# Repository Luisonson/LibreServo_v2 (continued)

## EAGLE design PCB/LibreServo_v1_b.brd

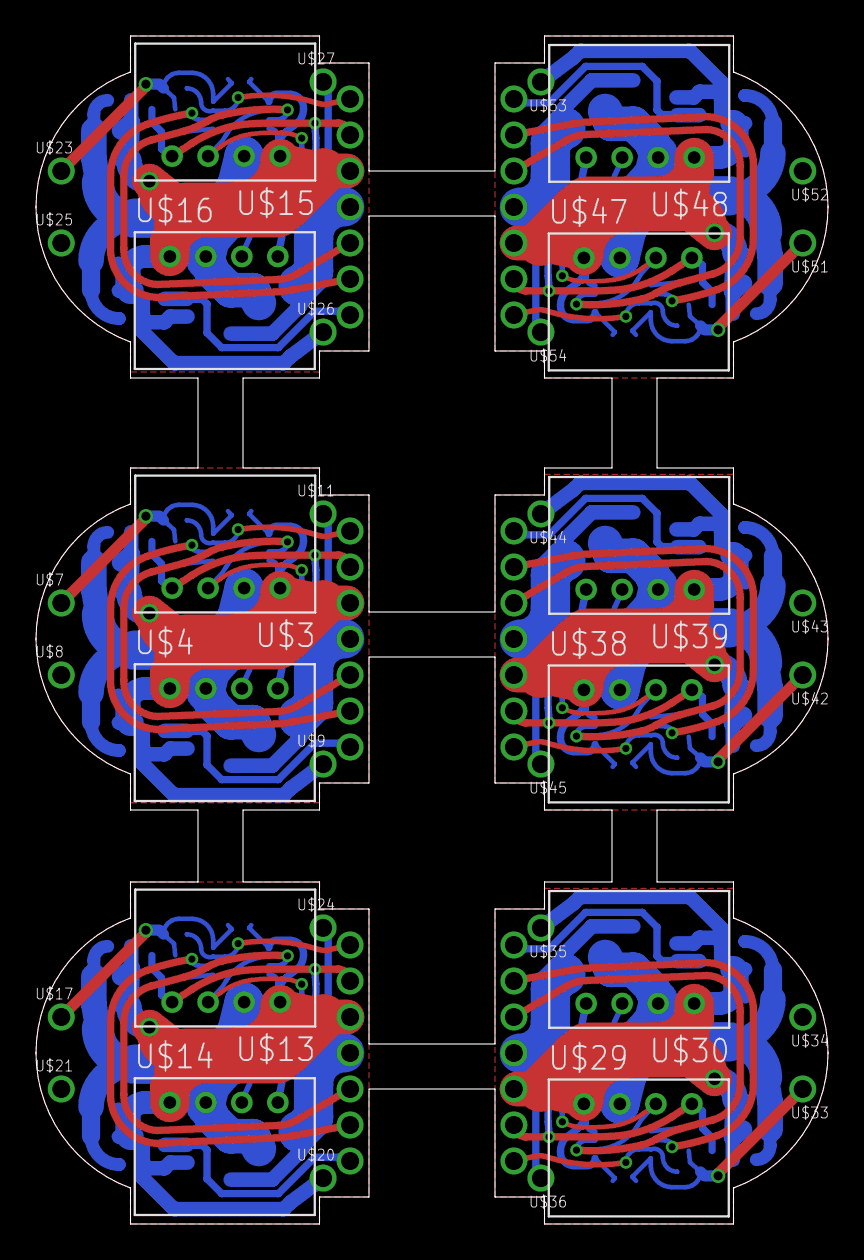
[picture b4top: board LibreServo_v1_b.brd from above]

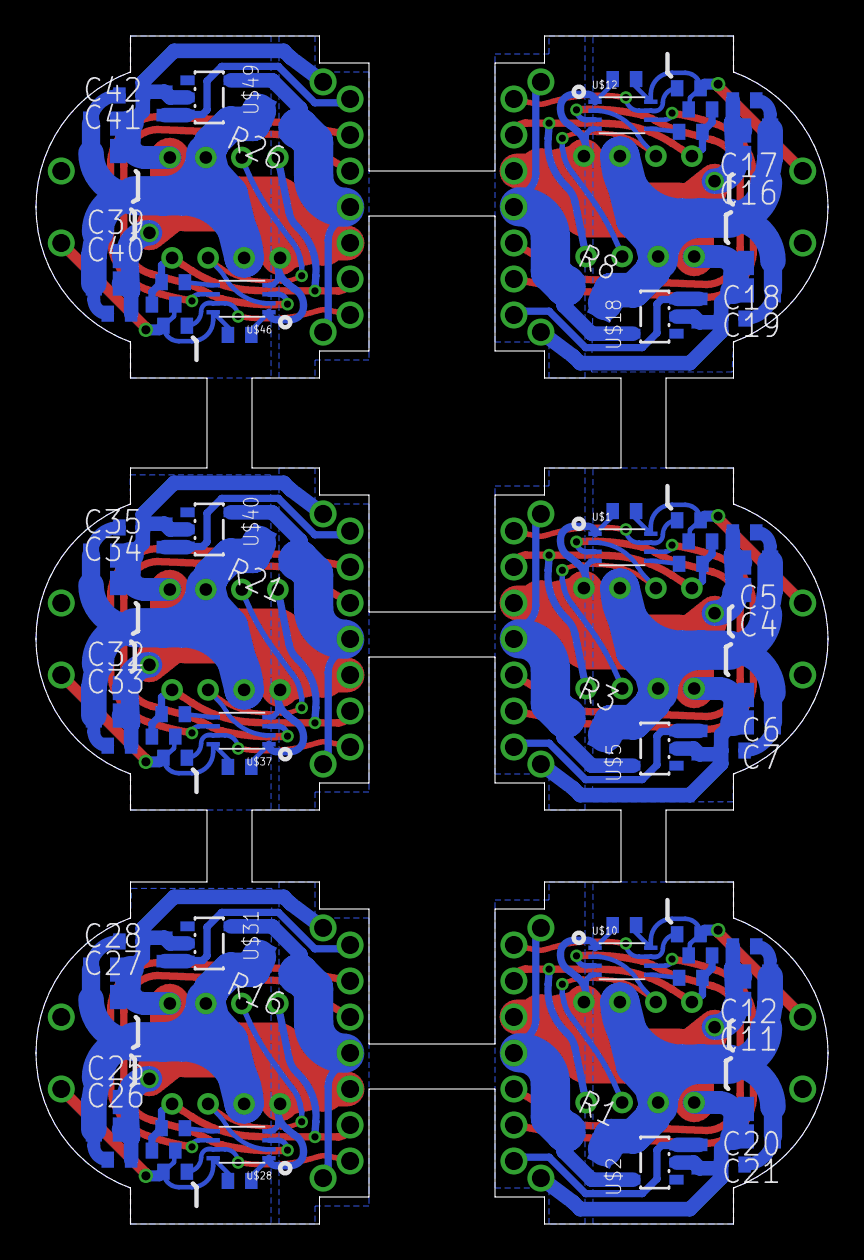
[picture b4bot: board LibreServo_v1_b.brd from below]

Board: 2 copper layers, 44.0 x 66.0 mm, 126 parts (84 on the bottom side), 66 nets.

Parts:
C1, C2, C3, C8, C9, C10, C13, C14, C15, C22, C23, C24, C29, C30, C31, C36, C37, C38: 100nF; C0402
C4, C5, C6, C7, C11, C12, C16, C17, C18, C19, C20, C21, C25, C26, C27, C28, C32, C33, C34, C35, C39, C40, C41, C42: 22uF; 0805_MIN
R1, R3, R8, R16, R21, R26: 0.02; 1206_ESTRECHA
R2, R4, R9, R17, R22, R27: 1k1; R0402
R5, R10, R11, R18, R23, R28: 10K; R0402
R6, R12, R14, R19, R24, R29: 100; R0402
R7, R13, R15, R20, R25, R30: 100K; R0402
U$1, U$10, U$12, U$28, U$37, U$46: SN74LVC2G125; VSSOP-8
U$2, U$5, U$18, U$31, U$40, U$49: ZXCT1010; SOT25
U$3, U$4, U$13, U$14, U$15, U$16, U$29, U$30, U$38, U$39, U$47, U$48: JST_PH-4; JST_PH-4_HOLE
U$6, U$19, U$22, U$32, U$41, U$50: HEADER_7_MIN
U$7, U$8, U$9, U$11, U$17, U$20, U$21, U$23, U$24, U$25, U$26, U$27, U$33, U$34, U$35, U$36, U$42, U$43, U$44, U$45, U$51, U$52, U$53, U$54: HEADER_1_MIN

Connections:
+3V3_1: C3.1, R5.1, R7.2, U$1.P$8, U$7.P$1
+3V3_2: C15.1, R11.1, R13.2, U$10.P$8, U$17.P$1
+3V3_3: C10.1, R10.1, R15.2, U$12.P$8, U$23.P$1
+3V3_4: C24.1, R18.1, R20.2, U$28.P$8, U$33.P$1
+3V3_5: C31.1, R23.1, R25.2, U$37.P$8, U$42.P$1
+3V3_6: C38.1, R28.1, R30.2, U$46.P$8, U$51.P$1
+7V_1: R3.1, U$5.5, U$6.P$4, U$11.P$1
+7V_2: R1.1, U$2.5, U$19.P$4, U$24.P$1
+7V_2_CABLE: C11.1, C12.1, C13.1, C14.1, C20.1, C21.1, R1.2, U$2.4, U$13.P$2, U$14.P$2
+7V_2_CABLE1: C1.1, C2.1, C4.1, C5.1, C6.1, C7.1, R3.2, U$3.P$2, U$4.P$2, U$5.4
+7V_2_CABLE2: C8.1, C9.1, C16.1, C17.1, C18.1, C19.1, R8.2, U$15.P$2, U$16.P$2, U$18.4
+7V_2_CABLE3: C22.1, C23.1, C25.1, C26.1, C27.1, C28.1, R16.2, U$29.P$2, U$30.P$2, U$31.4
+7V_2_CABLE4: C29.1, C30.1, C32.1, C33.1, C34.1, C35.1, R21.2, U$38.P$2, U$39.P$2, U$40.4
+7V_2_CABLE5: C36.1, C37.1, C39.1, C40.1, C41.1, C42.1, R26.2, U$47.P$2, U$48.P$2, U$49.4
+7V_3: R8.1, U$18.5, U$22.P$4, U$27.P$1
+7V_4: R16.1, U$31.5, U$32.P$4, U$36.P$1
+7V_5: R21.1, U$40.5, U$41.P$4, U$45.P$1
+7V_6: R26.1, U$49.5, U$50.P$4, U$54.P$1
EN_SERIAL_1: R5.2, U$1.P$7, U$6.P$1
EN_SERIAL_2: R11.2, U$10.P$7, U$19.P$1
EN_SERIAL_3: R10.2, U$12.P$7, U$22.P$1
EN_SERIAL_4: R18.2, U$28.P$7, U$32.P$1
EN_SERIAL_5: R23.2, U$37.P$7, U$41.P$1
EN_SERIAL_6: R28.2, U$46.P$7, U$50.P$1
GND1: C1.2, C2.2, C3.2, C4.2, C5.2, C6.2, C7.2, R4.1, U$1.P$1, U$1.P$4, U$3.P$1, U$4.P$1, U$5.2, U$6.P$3, U$9.P$1
GND2: C11.2, C12.2, C13.2, C14.2, C15.2, C20.2, C21.2, R2.1, U$2.2, U$10.P$1, U$10.P$4, U$13.P$1, U$14.P$1, U$19.P$3, U$20.P$1
GND3: C8.2, C9.2, C10.2, C16.2, C17.2, C18.2, C19.2, R9.1, U$12.P$1, U$12.P$4, U$15.P$1, U$16.P$1, U$18.2, U$22.P$3, U$26.P$1
GND4: C22.2, C23.2, C24.2, C25.2, C26.2, C27.2, C28.2, R17.1, U$28.P$1, U$28.P$4, U$29.P$1, U$30.P$1, U$31.2, U$32.P$3, U$35.P$1
GND5: C29.2, C30.2, C31.2, C32.2, C33.2, C34.2, C35.2, R22.1, U$37.P$1, U$37.P$4, U$38.P$1, U$39.P$1, U$40.2, U$41.P$3, U$44.P$1
GND6: C36.2, C37.2, C38.2, C39.2, C40.2, C41.2, C42.2, R27.1, U$46.P$1, U$46.P$4, U$47.P$1, U$48.P$1, U$49.2, U$50.P$3, U$53.P$1
unnamed: R6.1, U$1.P$5
unnamed: R14.1, U$12.P$5
unnamed: R19.1, U$28.P$5
unnamed: R24.1, U$37.P$5
unnamed: R29.1, U$46.P$5
unnamed: R12.1, U$10.P$5
RX_1: U$1.P$6, U$6.P$6
RX_2: U$10.P$6, U$19.P$6
RX_2_CABLE: U$10.P$2, U$13.P$3, U$14.P$3
RX_2_CABLE1: U$1.P$2, U$3.P$3, U$4.P$3
RX_2_CABLE2: U$12.P$2, U$15.P$3, U$16.P$3
RX_2_CABLE3: U$28.P$2, U$29.P$3, U$30.P$3
RX_2_CABLE4: U$37.P$2, U$38.P$3, U$39.P$3
RX_2_CABLE5: U$46.P$2, U$47.P$3, U$48.P$3
RX_3: U$12.P$6, U$22.P$6
RX_4: U$28.P$6, U$32.P$6
RX_5: U$37.P$6, U$41.P$6
RX_6: U$46.P$6, U$50.P$6
TX_1: U$1.P$3, U$6.P$5
TX_2: U$10.P$3, U$19.P$5
TX_2_CABLE: R12.2, R13.1, U$13.P$4, U$14.P$4, U$19.P$2
TX_2_CABLE1: R6.2, R7.1, U$3.P$4, U$4.P$4, U$6.P$2
TX_2_CABLE2: R14.2, R15.1, U$15.P$4, U$16.P$4, U$22.P$2
TX_2_CABLE3: R19.2, R20.1, U$29.P$4, U$30.P$4, U$32.P$2
TX_2_CABLE4: R24.2, R25.1, U$38.P$4, U$39.P$4, U$41.P$2
TX_2_CABLE5: R29.2, R30.1, U$47.P$4, U$48.P$4, U$50.P$2
TX_3: U$12.P$3, U$22.P$5
TX_4: U$28.P$3, U$32.P$5
TX_5: U$37.P$3, U$41.P$5
TX_6: U$46.P$3, U$50.P$5
V_CORRIENTE_1: R4.2, U$5.3, U$6.P$7
V_CORRIENTE_2: R2.2, U$2.3, U$19.P$7
V_CORRIENTE_3: R9.2, U$18.3, U$22.P$7
V_CORRIENTE_4: R17.2, U$31.3, U$32.P$7
V_CORRIENTE_5: R22.2, U$40.3, U$41.P$7
V_CORRIENTE_6: R27.2, U$49.3, U$50.P$7

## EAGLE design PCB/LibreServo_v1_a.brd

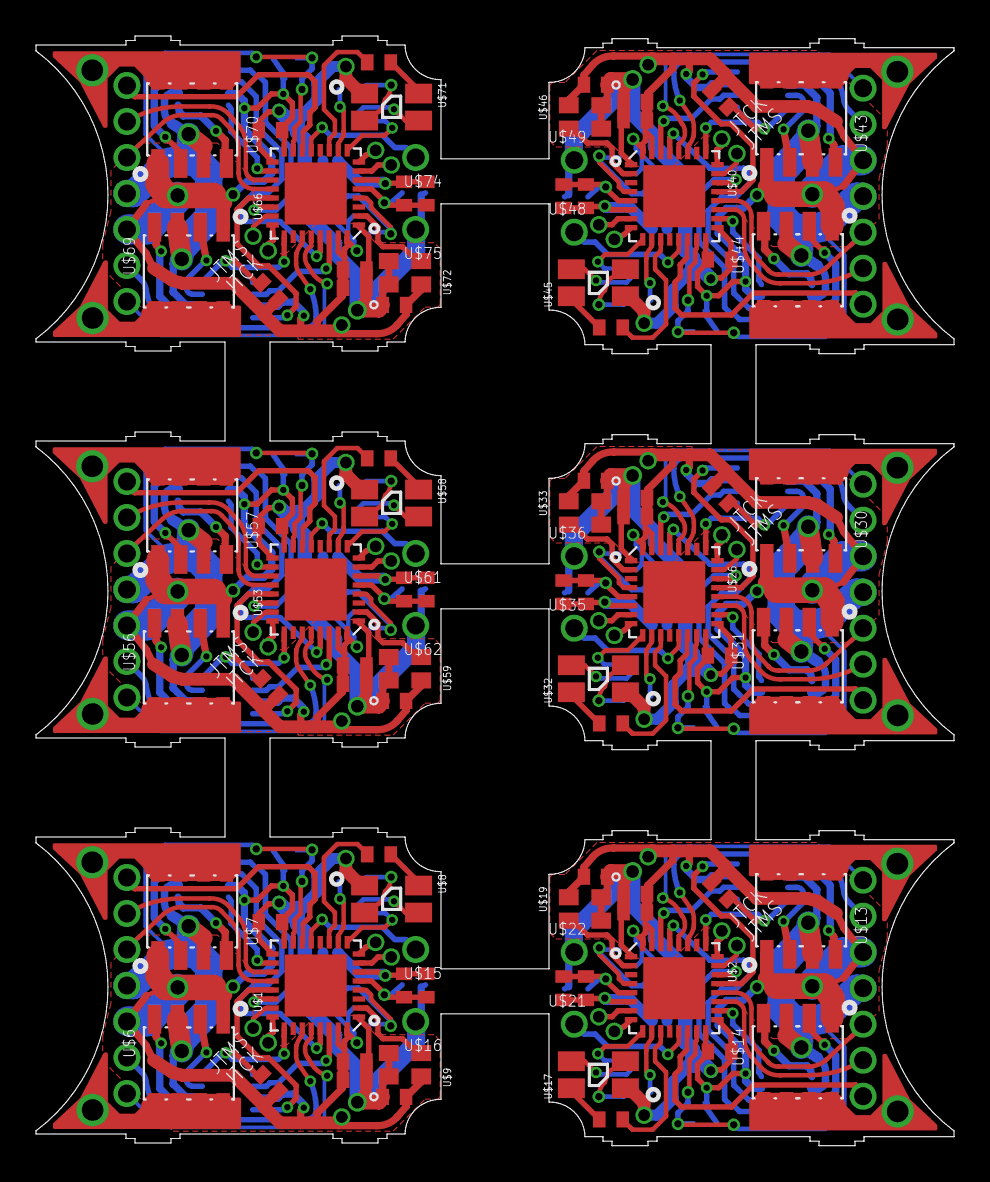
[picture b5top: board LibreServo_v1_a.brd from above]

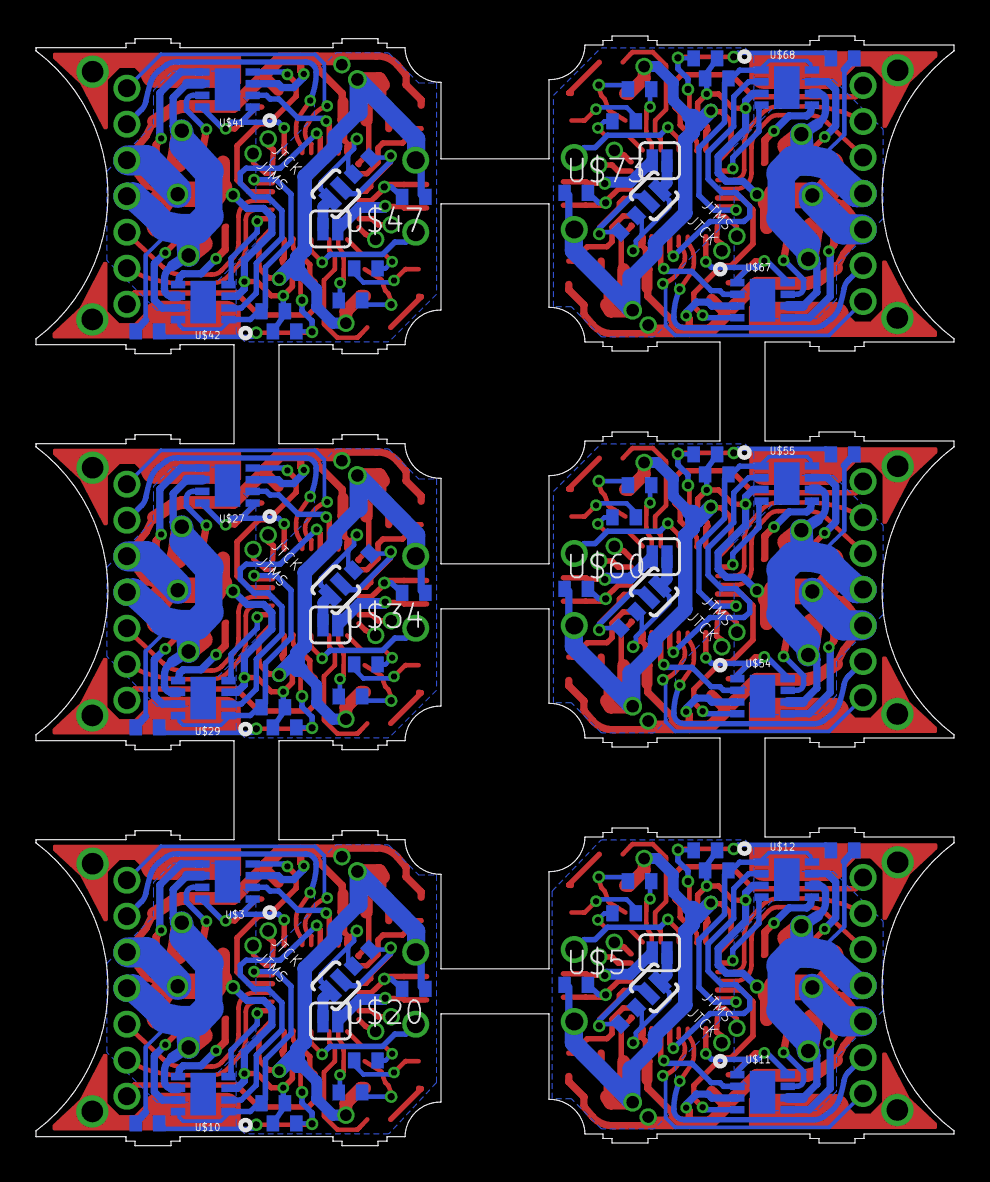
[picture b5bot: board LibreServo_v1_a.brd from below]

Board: 2 copper layers, 51.0 x 61.7 mm, 174 parts (66 on the bottom side), 192 nets.

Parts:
C1, C2, C4, C6, C7, C9, C11, C12, C13, C14, C16, C17, C19, C20, C21, C22, C24, C26, C27, C28, C29, C31, C33, C34, C35, C36, C38, C40, C41, C42: 100nF; C0402
C3, C8, C15, C23, C30, C37: 4.7uF; C0402
C5, C10, C18, C25, C32, C39: 1uF; C0402
R1, R3, R4, R5, R7, R9, R10, R11, R12, R13, R15, R16, R17, R19, R20, R21, R23, R24: 10K; R0402
R2, R6, R8, R14, R18, R22: 51K; R0402
R_BLUE, R_BLUE1, R_BLUE2, R_BLUE3, R_BLUE4, R_BLUE5: 470; R0402
R_GREEN, R_GREEN1, R_GREEN2, R_GREEN3, R_GREEN4, R_GREEN5: 300; R0402
R_RED, R_RED1, R_RED2, R_RED3, R_RED4, R_RED5: 330; R0402
SJ1, SJ3, SJ5, SJ7, SJ9, SJ11: SOLDAR; SJ_2S
SJ2, SJ4, SJ6, SJ8, SJ10, SJ12: NO-SOLDAR; SJ_2S-NO
U$1, U$2, U$26, U$40, U$53, U$66: STM32F302; QFN32
U$3, U$10, U$11, U$12, U$27, U$29, U$41, U$42, U$54, U$55, U$67, U$68: FAN3227/3; MLP8
U$4, U$24, U$38, U$51, U$64, U$77: PAD_LIBRE_SERVO_V1_A
U$5, U$20, U$34, U$47, U$60, U$73: FERRITA; 0402
U$6, U$7, U$13, U$14, U$30, U$31, U$43, U$44, U$56, U$57, U$69, U$70: FDS8858CZ; SO-8
U$8, U$17, U$32, U$45, U$58, U$71: RGB_PLCC4; PLCC4
U$9, U$19, U$33, U$46, U$59, U$72: OSC-8MHz; OSC-2.5X2
U$15, U$16, U$21, U$22, U$35, U$36, U$48, U$49, U$61, U$62, U$74, U$75: HEADER_1_MIN
U$18, U$23, U$37, U$50, U$63, U$76: HEADER_7_MIN
U$25, U$28, U$39, U$52, U$65, U$78: PAD_LIBRE_SERVO_V1_B

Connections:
+3V3_1: C1.2, C2.1, C3.2, C6.1, U$1.1, U$1.17, U$5.1, U$8.P$1, U$9.P$1, U$9.P$4, U$16.P$1
+3V3_2: C7.1, C8.2, C11.1, C12.2, U$2.1, U$2.17, U$17.P$1, U$19.P$1, U$19.P$4, U$20.1, U$22.P$1
+3V3_3: C14.1, C15.2, C19.1, C20.2, U$26.1, U$26.17, U$32.P$1, U$33.P$1, U$33.P$4, U$34.1, U$36.P$1
+3V3_4: C22.1, C23.2, C26.1, C27.2, U$40.1, U$40.17, U$45.P$1, U$46.P$1, U$46.P$4, U$47.1, U$49.P$1
+3V3_5: C29.1, C30.2, C33.1, C34.2, U$53.1, U$53.17, U$58.P$1, U$59.P$1, U$59.P$4, U$60.1, U$62.P$1
+3V3_6: C36.1, C37.2, C40.1, C41.2, U$66.1, U$66.17, U$71.P$1, U$72.P$1, U$72.P$4, U$73.1, U$75.P$1
+7V_1: R8.1, U$6.P$3, U$7.P$3, U$11.P$6, U$12.P$6, U$18.P$4
+7V_2: R2.1, U$3.P$6, U$10.P$6, U$13.P$3, U$14.P$3, U$23.P$4
+7V_3: R6.1, U$27.P$6, U$29.P$6, U$30.P$3, U$31.P$3, U$37.P$4
+7V_4: R14.1, U$41.P$6, U$42.P$6, U$43.P$3, U$44.P$3, U$50.P$4
+7V_5: R18.1, U$54.P$6, U$55.P$6, U$56.P$3, U$57.P$3, U$63.P$4
+7V_6: R22.1, U$67.P$6, U$68.P$6, U$69.P$3, U$70.P$3, U$76.P$4
EN_Q1: R9.2, U$1.25, U$11.P$1, U$11.P$8
EN_Q2: R10.1, U$1.22, U$12.P$1, U$12.P$8
EN_Q3: R3.2, U$2.25, U$3.P$1, U$3.P$8
EN_Q4: R4.1, U$2.22, U$10.P$1, U$10.P$8
EN_Q5: R11.2, U$26.25, U$27.P$1, U$27.P$8
EN_Q6: R12.1, U$26.22, U$29.P$1, U$29.P$8
EN_Q7: R15.2, U$40.25, U$41.P$1, U$41.P$8
EN_Q8: R16.1, U$40.22, U$42.P$1, U$42.P$8
EN_Q9: R19.2, U$53.25, U$54.P$1, U$54.P$8
EN_Q10: R20.1, U$53.22, U$55.P$1, U$55.P$8
EN_Q11: R23.2, U$66.25, U$67.P$1, U$67.P$8
EN_Q12: R24.1, U$66.22, U$68.P$1, U$68.P$8
EN_SERIAL_1: U$1.28, U$18.P$1
EN_SERIAL_2: U$2.28, U$23.P$1
EN_SERIAL_3: U$26.28, U$37.P$1
EN_SERIAL_4: U$40.28, U$50.P$1
EN_SERIAL_5: U$53.28, U$63.P$1
EN_SERIAL_6: U$66.28, U$76.P$1
GNDA: C4.2, C5.2, SJ1.2, U$1.6
GNDA1: C9.2, C10.2, SJ3.2, U$2.6
GNDA2: C17.2, C18.2, SJ5.2, U$26.6
GNDA3: C24.2, C25.2, SJ7.2, U$40.6
GNDA4: C31.2, C32.2, SJ9.2, U$53.6
GNDA5: C38.2, C39.2, SJ11.2, U$66.6
GND_1: C1.1, C2.2, C3.1, C6.2, C16.2, R7.2, R9.1, R10.2, SJ1.1, SJ2.1, U$1.16, U$1.31, U$1.32, U$6.P$1, U$7.P$1, U$9.P$2, U$11.P$3, U$12.P$3, U$18.P$3
GND_2: C7.2, C8.1, C11.2, C12.1, C13.2, R1.2, R3.1, R4.2, SJ3.1, SJ4.1, U$2.16, U$2.31, U$2.32, U$3.P$3, U$10.P$3, U$13.P$1, U$14.P$1, U$19.P$2, U$23.P$3
GND_3: C14.2, C15.1, C19.2, C20.1, C21.2, R5.2, R11.1, R12.2, SJ5.1, SJ6.1, U$26.16, U$26.31, U$26.32, U$27.P$3, U$29.P$3, U$30.P$1, U$31.P$1, U$33.P$2, U$37.P$3
GND_4: C22.2, C23.1, C26.2, C27.1, C28.2, R13.2, R15.1, R16.2, SJ7.1, SJ8.1, U$40.16, U$40.31, U$40.32, U$41.P$3, U$42.P$3, U$43.P$1, U$44.P$1, U$46.P$2, U$50.P$3
GND_5: C29.2, C30.1, C33.2, C34.1, C35.2, R17.2, R19.1, R20.2, SJ9.1, SJ10.1, U$53.16, U$53.31, U$53.32, U$54.P$3, U$55.P$3, U$56.P$1, U$57.P$1, U$59.P$2, U$63.P$3
GND_6: C36.2, C37.1, C40.2, C41.1, C42.2, R21.2, R23.1, R24.2, SJ11.1, SJ12.1, U$66.16, U$66.31, U$66.32, U$67.P$3, U$68.P$3, U$69.P$1, U$70.P$1, U$72.P$2, U$76.P$3
LED_BLUE: R_BLUE.2, U$1.11
LED_BLUE1: R_BLUE1.2, U$2.11
LED_BLUE2: R_BLUE2.2, U$26.11
LED_BLUE3: R_BLUE3.2, U$40.11
LED_BLUE4: R_BLUE4.2, U$53.11
LED_BLUE5: R_BLUE5.2, U$66.11
LED_GREEN: R_GREEN.2, U$1.9
LED_GREEN1: R_GREEN1.2, U$2.9
LED_GREEN2: R_GREEN2.2, U$26.9
LED_GREEN3: R_GREEN3.2, U$40.9
LED_GREEN4: R_GREEN4.2, U$53.9
LED_GREEN5: R_GREEN5.2, U$66.9
LED_RED: R_RED.2, U$1.10
LED_RED1: R_RED1.2, U$2.10
LED_RED2: R_RED2.2, U$26.10
LED_RED3: R_RED3.2, U$40.10
LED_RED4: R_RED4.2, U$53.10
LED_RED5: R_RED5.2, U$66.10
unnamed: R_BLUE.1, U$8.P$2
unnamed: R_GREEN.1, U$8.P$3
unnamed: R_RED.1, U$8.P$4
unnamed: U$2.2, U$19.P$3
unnamed: U$1.2, U$9.P$3
unnamed: U$3.P$7, U$13.P$2
unnamed: U$3.P$5, U$13.P$4
unnamed: U$6.P$2, U$11.P$7
unnamed: U$10.P$7, U$14.P$2
unnamed: U$10.P$5, U$14.P$4
unnamed: U$13.P$5, U$13.P$6, U$13.P$7, U$13.P$8, U$25.P$1, U$25.P$2
unnamed: U$6.P$4, U$11.P$5
unnamed: U$7.P$2, U$12.P$7
unnamed: U$14.P$5, U$14.P$6, U$14.P$7, U$14.P$8, U$24.P$1, U$24.P$2
unnamed: R_BLUE1.1, U$17.P$2
unnamed: U$7.P$4, U$12.P$5
unnamed: U$6.P$5, U$6.P$6, U$6.P$7, U$6.P$8, U$28.P$1, U$28.P$2
unnamed: R_GREEN1.1, U$17.P$3
unnamed: R_RED1.1, U$17.P$4
unnamed: U$26.2, U$33.P$3
unnamed: U$27.P$7, U$30.P$2
unnamed: U$4.P$1, U$4.P$2, U$7.P$5, U$7.P$6, U$7.P$7, U$7.P$8
unnamed: U$27.P$5, U$30.P$4
unnamed: U$29.P$7, U$31.P$2
unnamed: U$29.P$5, U$31.P$4
unnamed: U$30.P$5, U$30.P$6, U$30.P$7, U$30.P$8, U$39.P$1, U$39.P$2
unnamed: U$31.P$5, U$31.P$6, U$31.P$7, U$31.P$8, U$38.P$1, U$38.P$2
unnamed: R_BLUE2.1, U$32.P$2
unnamed: R_GREEN2.1, U$32.P$3
unnamed: R_RED2.1, U$32.P$4
unnamed: U$40.2, U$46.P$3
unnamed: U$41.P$7, U$43.P$2
unnamed: U$41.P$5, U$43.P$4
unnamed: U$42.P$7, U$44.P$2
unnamed: U$42.P$5, U$44.P$4
unnamed: U$43.P$5, U$43.P$6, U$43.P$7, U$43.P$8, U$52.P$1, U$52.P$2
unnamed: U$44.P$5, U$44.P$6, U$44.P$7, U$44.P$8, U$51.P$1, U$51.P$2
unnamed: R_BLUE3.1, U$45.P$2
unnamed: R_GREEN3.1, U$45.P$3
unnamed: R_RED3.1, U$45.P$4
unnamed: U$53.2, U$59.P$3
unnamed: U$54.P$7, U$56.P$2
unnamed: U$54.P$5, U$56.P$4
unnamed: U$55.P$7, U$57.P$2
unnamed: U$55.P$5, U$57.P$4
unnamed: U$56.P$5, U$56.P$6, U$56.P$7, U$56.P$8, U$65.P$1, U$65.P$2
unnamed: U$57.P$5, U$57.P$6, U$57.P$7, U$57.P$8, U$64.P$1, U$64.P$2
unnamed: R_BLUE4.1, U$58.P$2
unnamed: R_GREEN4.1, U$58.P$3
unnamed: R_RED4.1, U$58.P$4
unnamed: U$66.2, U$72.P$3
unnamed: U$67.P$7, U$69.P$2
unnamed: U$67.P$5, U$69.P$4
unnamed: U$68.P$7, U$70.P$2
unnamed: U$68.P$5, U$70.P$4
unnamed: U$69.P$5, U$69.P$6, U$69.P$7, U$69.P$8, U$78.P$1, U$78.P$2
unnamed: U$70.P$5, U$70.P$6, U$70.P$7, U$70.P$8, U$77.P$1, U$77.P$2
unnamed: R_BLUE5.1, U$71.P$2
unnamed: R_GREEN5.1, U$71.P$3
unnamed: R_RED5.1, U$71.P$4
NRST: C16.1, SJ2.2, U$1.4
NRST1: C13.1, SJ4.2, U$2.4
NRST2: C21.1, SJ6.2, U$26.4
NRST3: C28.1, SJ8.2, U$40.4
NRST4: C35.1, SJ10.2, U$53.4
NRST5: C42.1, SJ12.2, U$66.4
Q1_INA_N: U$1.30, U$11.P$2
Q1_INA_N1: U$2.30, U$3.P$2
Q1_INA_N2: U$26.30, U$27.P$2
Q1_INA_N3: U$40.30, U$41.P$2
Q1_INA_N4: U$53.30, U$54.P$2
Q1_INA_N5: U$66.30, U$67.P$2
Q2_INA_N: U$1.29, U$12.P$2
Q2_INA_N1: U$2.29, U$10.P$2
Q2_INA_N2: U$26.29, U$29.P$2
Q2_INA_N3: U$40.29, U$42.P$2
Q2_INA_N4: U$53.29, U$55.P$2
Q2_INA_N5: U$66.29, U$68.P$2
RX_1: U$1.19, U$18.P$6
RX_2: U$2.19, U$23.P$6
RX_3: U$26.19, U$37.P$6
RX_4: U$40.19, U$50.P$6
RX_5: U$53.19, U$63.P$6
RX_6: U$66.19, U$76.P$6
TIM1_CH1: U$1.18, U$12.P$4
TIM1_CH2: U$2.21, U$3.P$4
TIM1_CH3: U$2.18, U$10.P$4
TIM1_CH4: U$1.21, U$11.P$4
TIM1_CH5: U$26.21, U$27.P$4
TIM1_CH6: U$26.18, U$29.P$4
TIM1_CH7: U$40.21, U$41.P$4
TIM1_CH8: U$40.18, U$42.P$4
TIM1_CH9: U$53.21, U$54.P$4
TIM1_CH10: U$53.18, U$55.P$4
TIM1_CH11: U$66.21, U$67.P$4
TIM1_CH12: U$66.18, U$68.P$4
TX_1: U$1.20, U$18.P$5
TX_2: U$2.20, U$23.P$5
TX_3: U$26.20, U$37.P$5
TX_4: U$40.20, U$50.P$5
TX_5: U$53.20, U$63.P$5
TX_6: U$66.20, U$76.P$5
USART2_RX_1: U$1.27, U$18.P$2
USART2_RX_2: U$2.27, U$23.P$2
USART2_RX_3: U$26.27, U$37.P$2
USART2_RX_4: U$40.27, U$50.P$2
USART2_RX_5: U$53.27, U$63.P$2
USART2_RX_6: U$66.27, U$76.P$2
VBAT: R7.1, R8.2, U$1.15
VBAT1: R1.1, R2.2, U$2.15
VBAT2: R5.1, R6.2, U$26.15
VBAT3: R13.1, R14.2, U$40.15
VBAT4: R17.1, R18.2, U$53.15
VBAT5: R21.1, R22.2, U$66.15
VDD: C4.1, C5.1, U$1.5, U$5.2
VDD1: C9.1, C10.1, U$2.5, U$20.2
VDD2: C17.1, C18.1, U$26.5, U$34.2
VDD3: C24.1, C25.1, U$40.5, U$47.2
VDD4: C31.1, C32.1, U$53.5, U$60.2
VDD5: C38.1, C39.1, U$66.5, U$73.2
V_CORRIENTE_1: U$1.14, U$18.P$7
V_CORRIENTE_2: U$2.14, U$23.P$7
V_CORRIENTE_3: U$26.14, U$37.P$7
V_CORRIENTE_4: U$40.14, U$50.P$7
V_CORRIENTE_5: U$53.14, U$63.P$7
V_CORRIENTE_6: U$66.14, U$76.P$7
V_POT_1: U$1.13, U$15.P$1
V_POT_2: U$2.13, U$21.P$1
V_POT_3: U$26.13, U$35.P$1
V_POT_4: U$40.13, U$48.P$1
V_POT_5: U$53.13, U$61.P$1
V_POT_6: U$66.13, U$74.P$1

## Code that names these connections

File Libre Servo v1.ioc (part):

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Mcu.Name=STM32F302K(6-8)Ux
Mcu.Package=UFQFPN32
Mcu.UserName=STM32F302K8Ux
PA0.GPIOParameters=GPIO_Speed
PA0.GPIO_Speed=GPIO_SPEED_FREQ_LOW
PA0.Signal=S_TIM2_CH1_ETR
PA1.GPIOParameters=GPIO_Speed
PA1.GPIO_Speed=GPIO_SPEED_FREQ_LOW
PA1.Signal=S_TIM2_CH2
PA10.Mode=Asynchronous
PA10.Signal=USART1_RX
PA11.Signal=S_TIM1_CH4
PA12.GPIOParameters=GPIO_PuPd
PA12.GPIO_PuPd=GPIO_PULLDOWN
PA12.Signal=GPIO_Output
PA13.Signal=SYS_JTMS-SWDIO
PA14.Signal=SYS_JTCK-SWCLK
PA15.GPIOParameters=GPIO_PuPd
PA15.GPIO_PuPd=GPIO_PULLDOWN
PA15.Signal=GPIO_Output
PA2.Signal=GPIO_Output
PA3.Signal=GPIO_Output
PA4.Signal=GPIO_Output
PA6.Signal=SharedAnalog_PA6
PA7.Signal=SharedAnalog_PA7
PA8.Signal=S_TIM1_CH1
PA9.GPIOParameters=GPIO_FM6
PA9.GPIO_FM6=__NULL
PA9.Mode=Asynchronous
PA9.Signal=USART1_TX
PB0.Signal=SharedAnalog_PB0
PB3.Mode=Asynchronous
PB3.Signal=USART2_TX
PB4.Mode=Asynchronous
PB4.Signal=USART2_RX
PB5.GPIOParameters=GPIO_PuPd
PB5.GPIO_PuPd=GPIO_PULLUP
PB5.Signal=GPIO_Output
PB6.GPIOParameters=GPIO_FM6
PB6.GPIO_FM6=SYSCFG_CFGR1_I2C_PB6_FMP
PB6.Signal=GPIO_Output
PB7.GPIOParameters=GPIO_FM7
PB7.GPIO_FM7=SYSCFG_CFGR1_I2C_PB7_FMP
PB7.Signal=GPIO_Output
PF0-OSC_IN.Mode=HSE-External-Clock-Source
PF0-OSC_IN.Signal=RCC_OSC_IN
RCC.HSEPLLFreq_Value=8000000
RCC.HSE_VALUE=8000000
RCC.SYSCLKFreq_VALUE=72000000
RCC.SYSCLKSourceVirtual=RCC_SYSCLKSOURCE_PLLCLK
board=Libre Servo v1

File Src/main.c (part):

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  /* EEPROM Init */
  EE_Init();

  if(READ_PIN(GPIOB,LL_GPIO_PIN_7) == 0)		//Pin USART1_RX
  {
	  uint32_t tiempo_reset, tiempo_led;
	  int tiempo_flash_led;
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
	  tiempo_flash_led = 600;

	  GPIOA->BRR=LED_GREEN;				//Clear_pin
	  GPIOA->BRR=LED_RED;				//Clear_pin
	  GPIOA->BRR=LED_BLUE;				//Clear_pin

	  while (READ_PIN(GPIOB,LL_GPIO_PIN_7) == 0 && (ticks - tiempo_reset) < 6000)		//Wait 6 secs to restore LibreServo
	  {
		  if((ticks - tiempo_led) > tiempo_flash_led)
		  {
			  tiempo_led = ticks;
			  FLIP_PIN(GPIOA,LED_GREEN);
			  FLIP_PIN(GPIOA,LED_RED);
			  FLIP_PIN(GPIOA,LED_BLUE);
			  if(ciclo_led == FALSE) ciclo_led = TRUE;
			  else
			  {
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  LL_AHB1_GRP1_EnableClock(LL_AHB1_GRP1_PERIPH_GPIOA);
  LL_AHB1_GRP1_EnableClock(LL_AHB1_GRP1_PERIPH_GPIOB);
  /**ADC1 GPIO Configuration
  PA6   ------> ADC1_IN10
  PA7   ------> ADC1_IN15
  PB0   ------> ADC1_IN11
  */
  GPIO_InitStruct.Pin = LL_GPIO_PIN_6|LL_GPIO_PIN_7;
  GPIO_InitStruct.Mode = LL_GPIO_MODE_ANALOG;
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  /* USER CODE END TIM1_Init 2 */
  LL_AHB1_GRP1_EnableClock(LL_AHB1_GRP1_PERIPH_GPIOA);
  /**TIM1 GPIO Configuration
  PA8   ------> TIM1_CH1
  PA9   ------> TIM1_CH2
  PA11   ------> TIM1_CH1N
  PA12   ------> TIM1_CH2N
  */
  GPIO_InitStruct.Pin = LL_GPIO_PIN_8|LL_GPIO_PIN_9|LL_GPIO_PIN_11|LL_GPIO_PIN_12;
  GPIO_InitStruct.Mode = LL_GPIO_MODE_ALTERNATE;
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
  LL_AHB1_GRP1_EnableClock(LL_AHB1_GRP1_PERIPH_GPIOB);
  /**USART1 GPIO Configuration
  PB6   ------> USART1_TX
  PB7   ------> USART1_RX
  */
  GPIO_InitStruct.Pin = LL_GPIO_PIN_6|LL_GPIO_PIN_7;
  GPIO_InitStruct.Mode = LL_GPIO_MODE_ALTERNATE;
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
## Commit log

2018-06-24 Test de git
    Test de git
2018-07-03 Add files via upload
    Prueba Interrupt TIM17
2018-07-03 Test TIM17 Working
2018-07-04 Led with struct
2018-07-05 Uso de extern en variables...
2018-07-06 test TIM17
2018-07-06 TIM17 Prescaler config fix
2018-07-06 LEDs fix bugs
2018-07-06 LED testing
2018-07-09 Led Bug Fix And rainbow RGB
2018-07-09 UART_TX_DMA_a
2018-09-02 ignore
2018-09-02 Añadido ficheros PCB
2018-09-06 optimización
2018-10-10 LibreServo v1.c
2022-05-31 Add files via upload
    Beta Version. LibreServo v0.1
2022-06-12 Create test
2022-06-18 Create borrar
2023-01-20 Add files via upload
    Revised Code to LibreServo v2.1
2023-01-20 Add files via upload
    New version 2.1
2023-05-10 Rename PCB/LibreServo-v2.1.sch to PCB/old/LibreServo-v2.1.sch
2023-05-10 Rename PCB/LibreServo-v2.2.sch to PCB/old/LibreServo-v2.2.sch
2023-05-10 Rename PCB/LibreServo-v2.sch to PCB/old/LibreServo-v2.sch
2023-05-10 Rename PCB/LibreServo-v2.1.brd to PCB/old/LibreServo-v2.1.brd
2023-05-10 Rename PCB/LibreServo-v2.2.brd to PCB/old/LibreServo-v2.2.brd
2023-05-10 Rename PCB/LibreServo-v2.brd to PCB/old/LibreServo-v2.brd
2023-05-10 Hardware Final version. v2.3.1
2023-05-10 Create old
2023-05-10 Create folder
2024-07-08 Added the BOM file
2024-07-18 Create One Connector Bottom folder
